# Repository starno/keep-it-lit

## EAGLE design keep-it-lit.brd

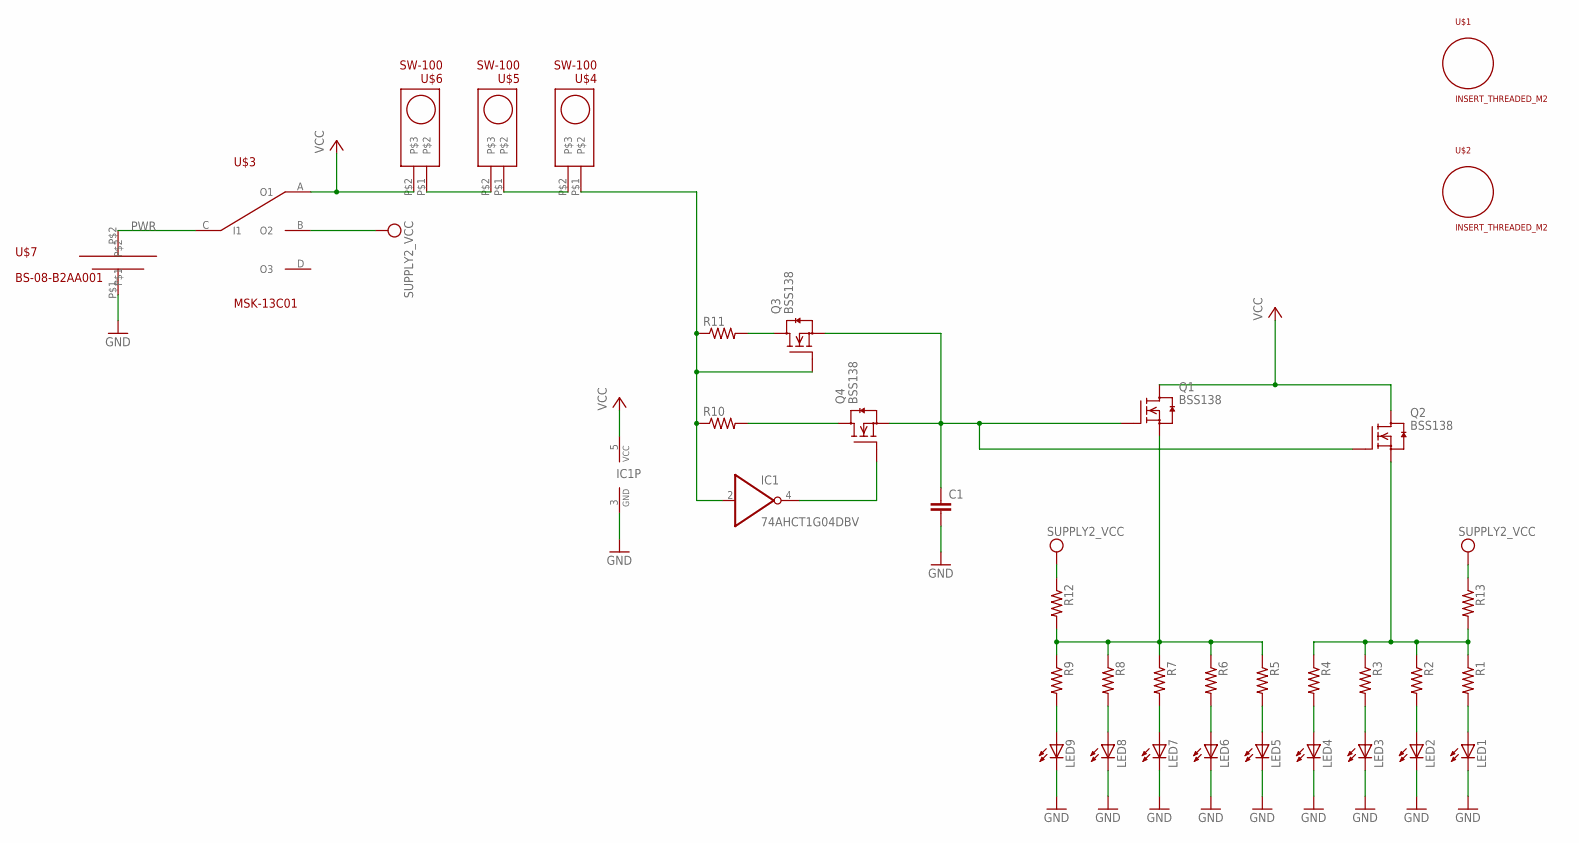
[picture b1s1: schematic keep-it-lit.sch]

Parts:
C1: CAP0603-CAP; 0603-CAP
IC1: 74AHCT1G04DBV; SOT23-5
LED1, LED2, LED3, LED4, LED5, LED6, LED7, LED8, LED9: LEDCHIPLED_1206; CHIPLED_1206
Q1, Q2, Q3, Q4: BSS138; SOT23
R1, R2, R3, R4, R5, R6, R7, R8, R9, R10, R11, R12, R13: RESISTOR0603-RES; 0603-RES
U$1, U$2: INSERT_THREADED_M2; INSERT_M2
U$3: MSK-13C01; SWITCH_SP3T
U$4, U$5, U$6: SW-100; SWITCH_TILT
U$7: BS-08-B2AA001; BATTERY_CONNECTOR_CR2032

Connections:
GND: C1.2, IC1.3 (GND), LED1.C, LED2.C, LED3.C, LED4.C, LED5.C, LED6.C, LED7.C, LED8.C, LED9.C, U$7.P$1
LED_GROUP1: Q1.2 (S), R5.1, R6.1, R7.1, R8.1, R9.1, R12.2
LED_GROUP2: Q2.2 (S), R1.1, R2.1, R3.1, R4.1, R13.2
unnamed: LED7.A, R7.2
unnamed: LED6.A, R6.2
unnamed: LED5.A, R5.2
unnamed: LED4.A, R4.2
unnamed: LED3.A, R3.2
unnamed: LED2.A, R2.2
unnamed: LED1.A, R1.2
unnamed: LED8.A, R8.2
unnamed: U$4.P$2, U$5.P$1
unnamed: U$5.P$2, U$6.P$1
unnamed: IC1.2 (I), Q3.1 (G), R10.1, R11.1, U$4.P$1
unnamed: IC1.4 (O), Q4.1 (G)
unnamed: Q3.3 (D), R11.2
unnamed: Q4.3 (D), R10.2
unnamed: C1.1, Q1.1 (G), Q2.1 (G), Q3.2 (S), Q4.2 (S)
unnamed: LED9.A, R9.2
PWR: U$3.C (I1), U$7.P$2
VCC: IC1.5 (VCC), Q1.3 (D), Q2.3 (D), U$3.A (O1), U$6.P$2
VCC_ALLON: R12.1, R13.1, U$3.B (O2)

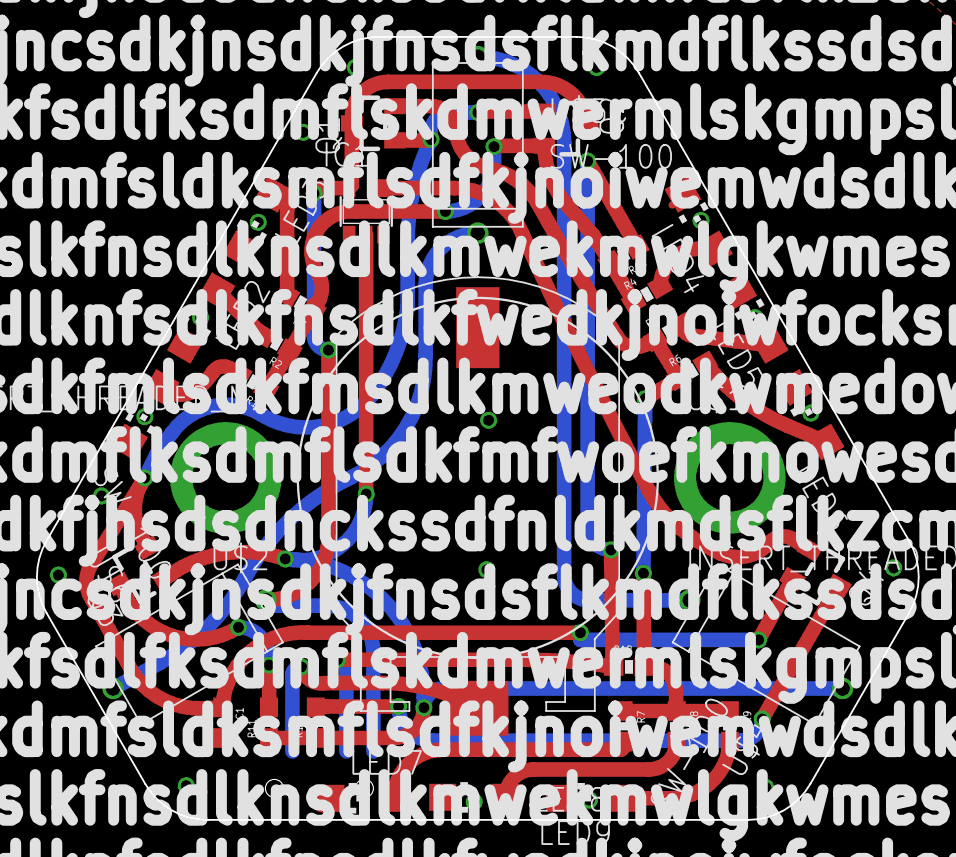
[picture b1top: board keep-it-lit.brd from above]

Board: 2 copper layers, 49.0 x 43.5 mm, 35 parts (1 on the bottom side), 22 nets.

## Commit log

2018-07-08 added lib, improved routing, fixed ground plane issues

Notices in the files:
parts and their libraries:
SparkFun-Passives: Licensing: Creative Commons ShareAlike 4.0 International - https://creativecommons.org/licenses/by-sa/4.0
